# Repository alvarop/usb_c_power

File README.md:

# USB-C-Power

Want to replace your non USB-C power/charge cables for USB-C ones? This project lets you do just that!

The board uses a [Cypress CYPD3177](https://www.cypress.com/file/460416/download) which will communicate with the USB power supply over USB-PD and negotiate the desired voltage and current. The voltage and current requested is set using 8 resistors that can be easily hand soldered to customize each one.

The available voltage ranges are: 5V, 9V, 12V, 15V, 19V, and 20V. You can set a minimum and maximum voltages in order to get the highest available or select just a single one so that you always know what you're getting.

The available currents range from : 0A to 5A in 0.25A increments.

If the selected voltage or current is not available, a red LED lights up and the output is disabled.

Trying to figure out which resistors to put where? Don't worry! I put together a nice calculator to do it for you. [Check it out here!](https://alvarop.com/usb_c_power/)

This board is designed to handle 5A @ 20V, but has only been tested to 3A @ 20V, so proceed with caution if you need the full 100W.

Want to build your own? Go to the [releases](https://github.com/alvarop/usb_c_power/releases) to get the files for latest stable version.

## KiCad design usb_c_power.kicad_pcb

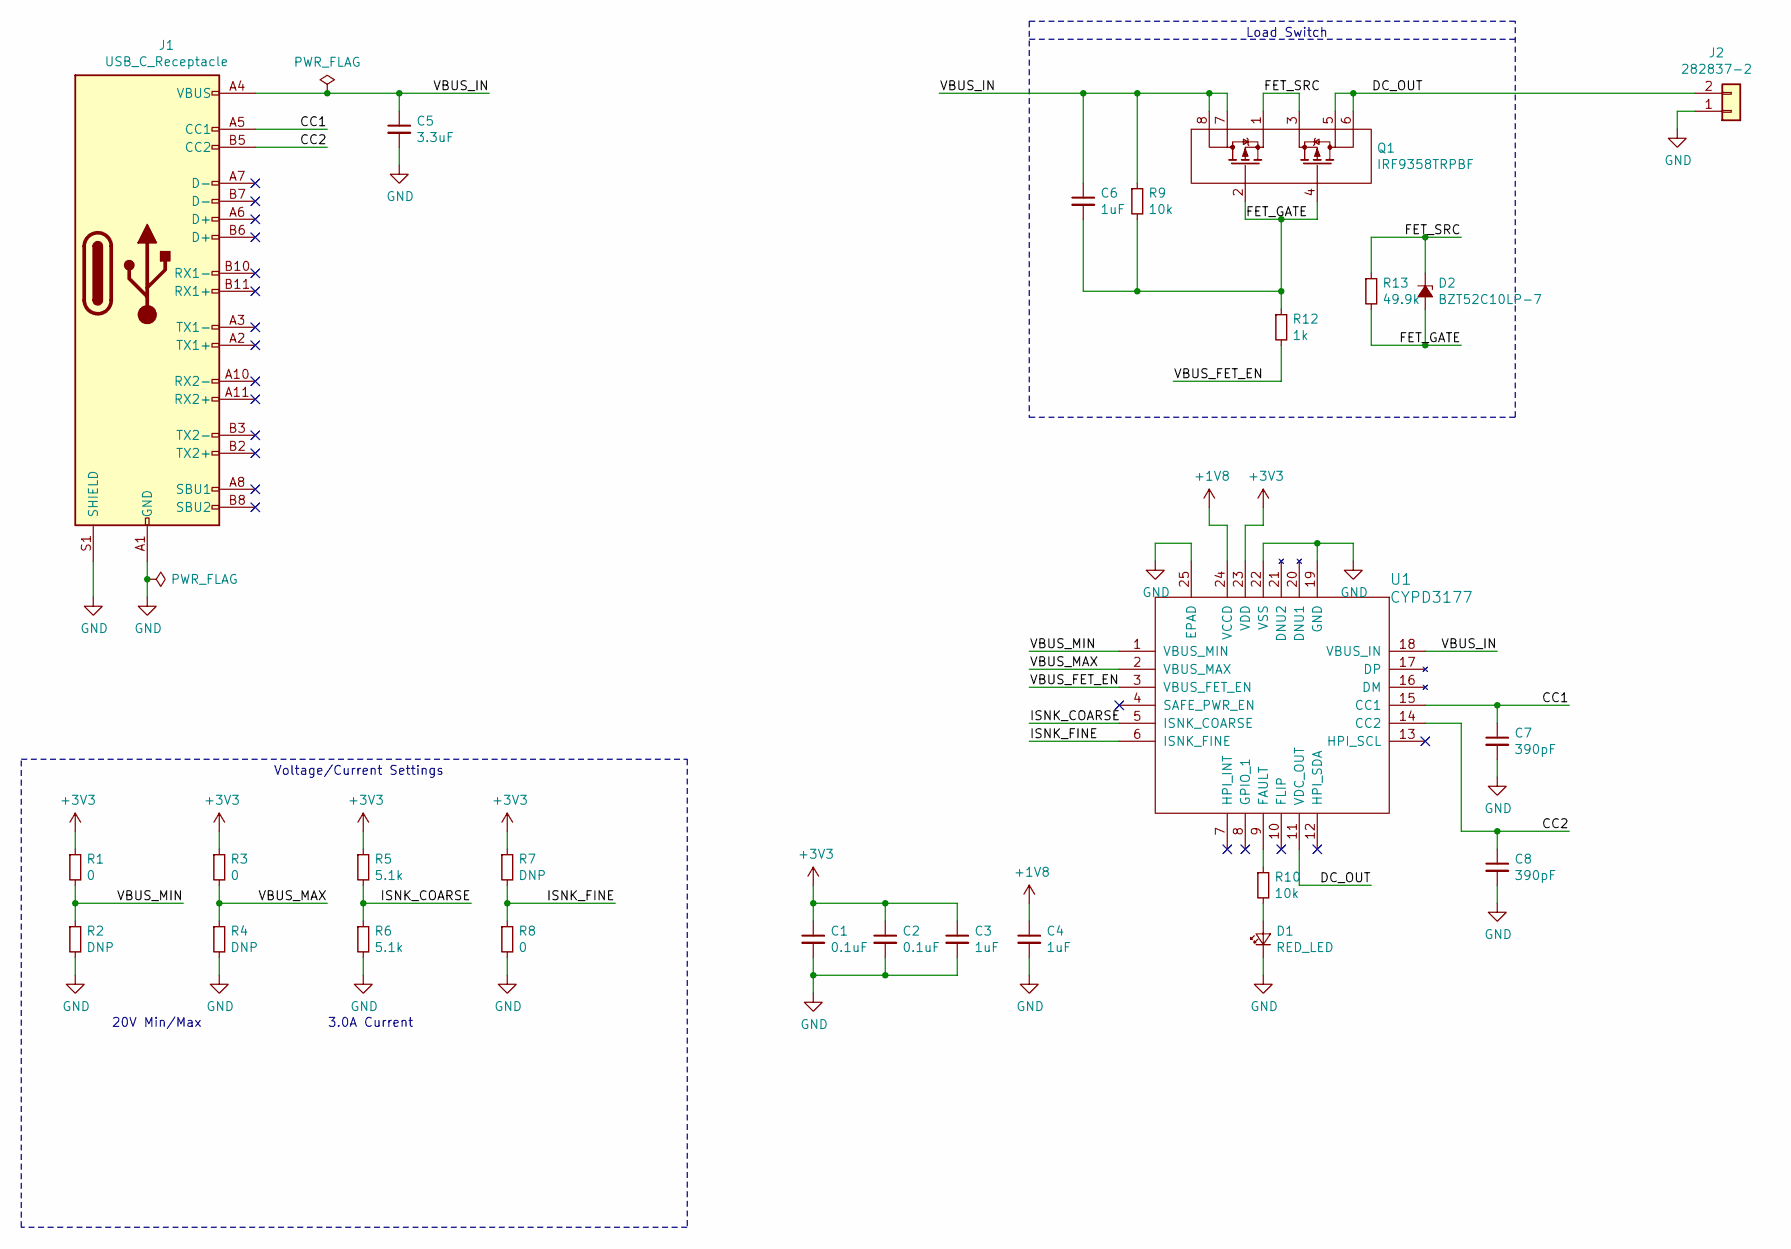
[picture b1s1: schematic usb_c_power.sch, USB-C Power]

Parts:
C1, C2: 0.1uF; C_0402_1005Metric; Voltage - Rated 10V; MPN GRM155R61A104KA01D
C3, C4: 1uF; C_0402_1005Metric; Voltage - Rated 16V; MPN CL05A105KO5NNNC
C5: 3.3uF; C_1210_3225Metric; Voltage - Rated 50V; MPN CGA6P3X7R1H335K250AB
C6: 1uF; C_0402_1005Metric; Voltage - Rated 35V; MPN C1005X5R1V105K050BE
C7, C8: 390pF; C_0402_1005Metric; MPN CL05B391KB5NNNC
D1: RED_LED; LED_0603_1608Metric; MPN SML-D12U1WT86
D2: BZT52C10LP-7; D_0402_1005Metric; MPN BZT52C10LP-7
J1: USB_C_Receptacle; MOLEX-1054500101; MPN 1054500101
J2: ‎282837-2‎; MPN 282837-2
Q1: IRF9358TRPBF; SO-8_3.9x4.9mm_P1.27mm; MPN IRF9358TRPBF
R1, R3, R8: 0; R_0805_2012Metric_Pad1.15x1.40mm_HandSolder; MPN RMCF0805ZT0R00
R2, R4, R7: DNP; R_0805_2012Metric_Pad1.15x1.40mm_HandSolder
R5, R6: 5.1k; R_0805_2012Metric_Pad1.15x1.40mm_HandSolder; MPN RMCF0805JT5K10
R9, R10: 10k; R_0402_1005Metric; MPN RC0402JR-0710KL
R12: 1k; R_0402_1005Metric; MPN CRG0402J1K0
R13: 49.9k; R_0402_1005Metric; MPN RC0402FR-0749K9L
U1: CYPD3177; QFN-24-1EP_4x4mm_P0.5mm_EP2.8x2.8mm; MPN CYPD3177-24LQXQ

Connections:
+1V8: C4.1, U1.24 (VCCD)
+3V3: C1.1, C2.1, C3.1, R1.1, R3.1, R5.1, R7.1, U1.23 (VDD)
/CC1: C7.1, J1.A5 (CC1), U1.15 (CC1)
/CC2: C8.1, J1.B5 (CC2), U1.14 (CC2)
/DC_OUT: J2.2, Q1.5, Q1.6, U1.11 (VDC_OUT)
/FET_GATE: C6.2, D2.2 (A), Q1.2, Q1.4, R9.2, R12.1, R13.2
/FET_SRC: D2.1 (K), Q1.1, Q1.3, R13.1
/ISNK_COARSE: R5.2, R6.1, U1.5 (ISNK_COARSE)
/ISNK_FINE: R7.2, R8.1, U1.6 (ISNK_FINE)
/VBUS_FET_EN: R12.2, U1.3 (VBUS_FET_EN)
/VBUS_IN: C5.1, C6.1, J1.A4 (VBUS), J1.A9 (VBUS), J1.B4 (VBUS), J1.B9 (VBUS), Q1.7, Q1.8, R9.1, U1.18 (VBUS_IN)
/VBUS_MAX: R3.2, R4.1, U1.2 (VBUS_MAX)
/VBUS_MIN: R1.2, R2.1, U1.1 (VBUS_MIN)
GND: C1.2, C2.2, C3.2, C4.2, C5.2, C7.2, C8.2, D1.1 (K), J1.A1 (GND), J1.A12 (GND), J1.B1 (GND), J1.B12 (GND), J1.S1 (SHIELD), J2.1, R2.2, R4.2, R6.2, R8.2, U1.19 (GND), U1.22 (VSS), U1.25 (EPAD)
unnamed: D1.2 (A), R10.2
unnamed: R10.1, U1.9 (FAULT)

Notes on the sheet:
20V Min/Max
3.0A Current
Voltage/Current Settings
Load Switch

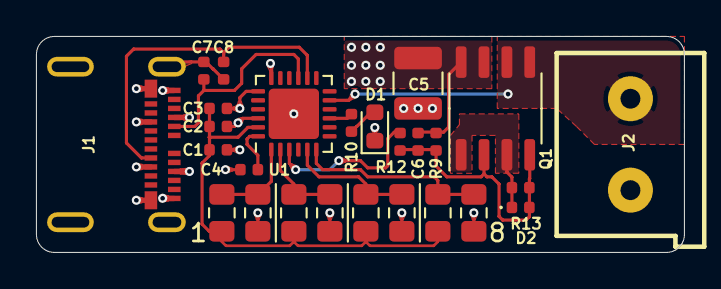
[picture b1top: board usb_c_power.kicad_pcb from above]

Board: 2 copper layers, 36.0 x 12.0 mm, 26 parts (0 on the bottom side), 16 nets.

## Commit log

2020-03-08 Initial commit. First draft of schematic
2020-03-08 Schematic tentatively finished.
    Footprints assigned and component details added
2020-03-09 Finished board and ordered from oshpark/oshstencil
2020-03-20 Adding CERN-OHL-P license
    https://ohwr.org/project/cernohl/wikis/faq
    https://ohwr.org/project/cernohl/wikis/uploads/0be6f561d2b4a686c5765c74be32daf9/CERN_OHL_rationale.pdf
2020-03-21 Created v1.1 * much larger (0805) setting resistors * 5A rated USB-C connector * Smaller 10V zener * Paste-in-hole for usb-c
2020-03-23 Finished v1.1 and ordered from oshpark
2020-07-17 Adding index.html and images
2020-07-17 Fix image base
2020-07-21 minor updates
2020-07-22 Trying different style
2020-07-22 minor tweaks to docs
2020-07-22 Adding error message to calculator
2020-07-22 Adding readme
